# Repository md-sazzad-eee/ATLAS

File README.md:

# ATLAS — Phase 1 foundation

Modular multi-robot research assistant: a carrier (ATLAS-M) that transports two agents
(ATLAS-S1 Scout, ATLAS-S2 Research), deploys them, collects their results, re-plans when
something fails, and tracks which conclusions depend on which evidence.

Phase 1 is the design and simulation stage. Nothing here is a measured hardware result.
Every number comes from `00_requirements/atlas_params.yaml` and is a **proposed target**.

## One source of truth

```
00_requirements/atlas_params.yaml   <- edit this only
python3 00_requirements/sync_params.py   -> atlas_params.json (+ interface checks)
```

MATLAB, FreeCAD and the Python simulator all read `atlas_params.json`. `sync_params.py`
refuses inconsistent interfaces, for example funnels that overlap, wheels that hit the
bays, or a bay shorter than the agent.

## What is here and how to run it

| Area | Tool | Entry point | Output |
|---|---|---|---|
| Drivetrain + energy sizing | MATLAB | `05_simulation/matlab/atlas_sizing.m` | `results/sizing_report.txt`, plots |
| Wheel-speed control loop | Simulink | `05_simulation/matlab/build_speed_loop.m` | `atlas_wheel_speed_loop.slx`, step/load plot |
| Docking state machine | Stateflow | `build_docking_fsm.m`, then `run_docking_tests.m` | `atlas_docking_fsm.slx`, 8 scenario tests, traces |
| Dock contact heating | MATLAB PDE Toolbox | `05_simulation/matlab/contact_heating.m` | `results/contact_heating.*` |
| Parametric CAD | FreeCAD | `01_mechanical/scripts/build_atlas_cad.py` | `.FCStd`, STEP, test-coupon STL, `cad_check.json` |
| Mission intelligence + fleet sim | Python | `05_simulation/python/run_experiments.py` | `results/summary.md`, plot |
| Tests | pytest | `cd 05_simulation/python && python3 -m pytest` | 33 tests |

To run FreeCAD, execute the script from FreeCAD's Python console:
`exec(open('<ATLAS>/01_mechanical/scripts/build_atlas_cad.py').read(), {'__file__': '<that path>'})`

Python needs `numpy scipy networkx pyyaml pydantic matplotlib pytest`.

## Phase 1 findings (what the models changed)

1. **Skid-steer turning sets the carrier motor size.** An in-place turn needs about 3.7×
   the straight-line torque. Widening the track from 300 to 400 mm cut that requirement
   from 0.80 to 0.64 N·m per wheel. Spec per wheel: at least 0.64 N·m continuous and at
   least 95 rpm loaded.
2. **The dock ramp sets the agent motor size.** Climbing the 12° ramp needs 3× the
   flat-floor torque. Spec per wheel: at least 0.10 N·m continuous and at least 73 rpm.
3. **The interface checks caught three geometry errors:**
   - Carrier wheels intruded into the bays, so the wheels moved outboard.
   - The bay was shorter than the agent, so the guides were lengthened to 120 mm.
   - The side latch hit the chassis wall and the neighbouring bay, so it was redesigned
     as a front catch-tab latch. The new latch needed 9.5 mm of pin travel against 8 mm
     available, so the travel spec is now 10 mm.
4. **Contact heating:** about 48 °C at 1 A with a healthy contact. A contaminated contact
   (200 mΩ) reaches about 177 °C at 2 A. Board C should therefore measure the voltage
   drop across the contacts and inhibit charging above about 100 mΩ. Print the contact
   block in PETG, ASA or nylon, not PLA.
5. **Evidence-aware re-planning** (300 paired Monte-Carlo runs). In runs with sensor
   drift:
   - Wrong conclusions: 21% of runs with reassignment alone, 0% with evidence-aware
     re-planning.
   - Recovery cost: about half the re-measurements of a "redo everything" policy, and
     about 3 minutes shorter missions.
   - The carrier never moved with an unlatched agent and no battery-reserve violations
     occurred across all runs.
6. **The batteries are oversized for a 30-minute target:** the agents have about 5 h of
   runtime and the carrier about 6 h. Either downsize (for example a 2S 1000 mAh agent
   pack) or raise the runtime target. Recharging both agents from the carrier uses 40% of
   the carrier's energy.

## Verification done

- The Stateflow chart passes 8 fault scenarios with 3 safety invariants checked on every sample.
- The Python docking FSM reproduces the Stateflow traces sample-for-sample (parity test).
  A deliberate mutation of the Python FSM makes that test fail, so the test does detect differences.
- The FreeCAD interference and clearance report is in `01_mechanical/docking_system/cad_check.json`.
- The blueprint §11 acceptance tests run as simulation tests in `tests/test_blueprint_section11.py`.

## Subsystems

### Dock contact heating (COMSOL)
- `05_simulation/comsol/ContactHeating.java` reproduces the MATLAB result (θ = 156 K/W, 47.8 °C at 1 A, 177 °C at 2 A / 200 mΩ).
- A realistic model that includes the agent side gives 43.6 °C at the design point and 105.7 °C with a contaminated contact.
- `AddPlots.java` adds the temperature and current-density plots to both saved models.

### Camera
ESP32-S3 on every agent. The Scout adds a power-gated Raspberry Pi Zero 2 W + Camera Module 3
(`07_documentation/camera_architecture.md`). Scout runtime with the camera on is about 3.7 h (`atlas_sizing.m`, params v0.1.3).

### Electronics (KiCad, `02_electronics/`)
Every board is specified in Python; the schematic is generated from the spec and the exported netlist is checked against it pin-for-pin.

| Board | Function | Layers | Result |
|---|---|---|---|
| B: agent controller | ESP32-S3, motors, encoders, camera power | 2 | ERC 0/0, DRC 0 errors, 0 unconnected, fab outputs |
| C: dock / charge interface | CC/CV charger per bay, 4-wire contact-resistance monitor | 2 | ERC 0/0, DRC 0 errors, 0 unconnected, fab outputs |
| A: carrier controller | ESP32-S3, 4 wheel drivers, bay interlock in hardware | 4 | ERC 0 errors, DRC 0 errors, 0 unconnected, fab outputs |

Board A puts the "never move with a seated, unlatched agent" rule into logic gates; Board C measures dock contact
resistance by 4-wire sensing. Details and the PCB flow are in `02_electronics/README.md`.

### Firmware (`03_firmware/`)
Agent and carrier application cores in plain C, host-tested against plant models (6022 + 42 + 28 checks, 0 failures).
ESP-IDF ports for Board B and Board A compile with 0 warnings; the Pi Zero vision service has 11 tests.

### ROS 2
A six-package ROS 2 (Jazzy) workspace exists but is not included in this repository yet.

## Further findings

1. The agent's series diode limits a dock charge to about 86 % SOC. An ideal diode on Board B rev B would reach 98 %.
2. Yaw from a single 50 mm AprilTag is unreliable beyond about 0.75 m. Dock alignment should steer on bearing when far out.
3. A 2 s heartbeat timeout lets an agent travel about 0.4 m blind.

## Next phase (bench work)

- Order and assemble Boards A, B and C; flash the ESP32 firmware.
- Motor identification (the agent and carrier PI gains use assumed motors).
- INA226 / ADC calibration and camera calibration.
- Print the clearance coupons; run 100 docking cycles.
- Charge tests with real contacts.

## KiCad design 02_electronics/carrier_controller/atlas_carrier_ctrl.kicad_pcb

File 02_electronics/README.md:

# Electronics

## Board B: ATLAS-S agent controller (shared by S1 and S2), rev A

KiCad 10 project: `agent_controller/atlas_agent_ctrl.kicad_pro`
Design source of truth: `agent_controller/design/board_b_design.py`, which holds every part, value, footprint and pin→net assignment.

| Check | Result |
|---|---|
| Parts / nets | 112 parts, 69 signal nets + 8 intentional no-connects |
| ERC (kicad-cli) | **0 errors, 0 warnings** |
| Schematic vs design spec | `design/verify_netlist.py`: **69/69 nets identical, pin-for-pin** |
| PCB placement | 110 × 90 mm, 2-layer, 4× M3. Courtyard check passes with no overlaps and no off-board parts. ESP32 antenna is flush with the front edge, with a keep-out band |
| Routing | Freerouting 2.1 (local, headless) via `design/run_pcb_pipeline.sh`: 1117 segments, 321 vias, **0 unrouted** |
| DRC (kicad-cli, with schematic parity) | **0 errors, 0 unconnected, 0 parity issues**; 8 cosmetic silkscreen warnings |
| Mechanical fit | Board inside the Scout body (FreeCAD): 5.2 mm above the wheels, 17.4 mm under the lid, 6 mm behind the front wall (`fit_check.json`) |
| Fab outputs | `fab/atlas_agent_ctrl_gerbers.zip` (gerbers + drill), `fab/atlas_agent_ctrl_bom.csv`, `fab/atlas_agent_ctrl_pos.csv`, `atlas_agent_ctrl.step` |

### Architecture

- **Power in:** 2S Li-ion (J1, with NTC), then a 3 A PTC, then a reverse-polarity P-MOSFET (AOD409), then a TVS (SMBJ10CA) and 100 µF bulk.
- **Dock charge path:** J2 pads (VCHG, GND, DATA, ID), then an SS34 diode (no backfeed to the pads), then the charge switch Q2, which the ESP32 can open (`CHG_EN`).
  - The ID resistor R8 sets agent identity: 10 k for S1, 22 k for S2.
  - DATA is a half-duplex UART with 1 k series resistors and ESD protection.
  - Note: the diode drop limits the pack to about 8.0 V (about 90% charge). This is deliberate and conservative.
- **Rails:**
  - **5 V / 3 A:** TPS563201 buck, Vout = 0.768 × (1 + 56k/10k) = 5.07 V. Feeds the Pi module and the sensor connector.
  - **3.3 V / 600 mA:** AP2112K LDO, fed from 5 V or USB VBUS through Schottky OR diodes, so the board can be programmed from USB without a battery.
- **MCU:** ESP32-S3-WROOM-1-N8R8 with native USB-C (ESD-protected), RESET and BOOT buttons, and a UART0 debug header.
  - GPIO35–37 are left unconnected because the N8R8 uses them for octal PSRAM.
  - Strapping pins 45 and 46 are left unconnected.
- **Motors:**
  - Two DRV8871 drivers with ILIM 33 k, giving about 2.0 A current limiting (assumed stall about 1.2 A from the MATLAB sizing).
  - A 20 mΩ high-side shunt feeds an INA180A2 (×50) per motor, so 1 A reads as 1.0 V at the ADC.
  - Encoders have 10 k pull-ups.
- **Independent motor disable:**
  - The motor rail VM_SW is switched by the P-MOSFET Q5.
  - Q5 turns on only when the 74LVC1G08 AND gate sees both `MOT_EN` (firmware) and `WDT_OK` (TPS3823 watchdog, 1.6 s timeout).
  - If the firmware hangs, the motors lose power without any software involved.
- **Scout vision module:** J6 (JST-GH 6P) carries power-gated 5 V and a UART to a Raspberry Pi Zero 2 W + Camera Module 3. See `07_documentation/camera_architecture.md`.
- **Expansion:** Qwiic I2C (J7) for IMU/ToF, and an 8-pin sensor-module connector (J8: 5 V, 3.3 V, I2C, GPIO, ADC) for the Research agent's instrument.
- **Test points:** VBAT, 5 V, 3V3, VM_SW, IMOT_L, IMOT_R, WDT_OK, GND.

### ESP32-S3 pin map

| GPIO | Net | GPIO | Net |
|---|---|---|---|
| 1/2 | I2C SDA/SCL | 15/16 | MOT_L IN1/IN2 |
| 4 | VBAT_SENSE (100k/22k) | 17/18 | LED_STAT / PI_PWR_EN |
| 5/6 | IMOT_L / IMOT_R | 21 | MOT_EN |
| 7 | BATT_NTC | 38 | WDI (watchdog kick) |
| 8 | DOCK_VSENSE | 39/40 | DOCK_TX / DOCK_RX |
| 9/10 | SENS_ADC / SENS_GPIO | 41 | CHG_EN |
| 11/12 | ENC_L A/B | 42 | MOT_R IN2 |
| 13/14 | ENC_R A/B | 47 | MOT_R IN1 |
| 19/20 | USB D−/D+ | 48 / 3 | PI_TX / PI_RX |

*Rev A1: the right-motor inputs moved to right-side module pins (IO47/IO42), swapping with LED_STAT/PI_PWR_EN, because the router could not cross the board from the left-side pins.*

### Rebuilding the board

`design/run_pcb_pipeline.sh` (macOS) runs the whole flow:
1. Place the parts from the spec.
2. Route with Freerouting.
3. Import the routes and add the GND pours and stitching vias.
4. Run up to 3 completion passes for any connection the router missed.
5. Bridge any isolated GND islands.
6. Run DRC.

The spec, the placement and the pipeline are the source. The `.kicad_pcb` is a generated output.
Routing needs a Java 21 runtime; the pipeline uses COMSOL's bundled JRE.

Layout choices:
- **Inset outline for routing.** Freerouting only keeps its 0.2 mm track clearance to the outline, so the DSN is exported with the outline inset 0.4 mm. This gives at least 0.6 mm copper-to-edge on the finished board.
- **GND plane, not routed.** GND is a plane on B.Cu plus a pour on F.Cu, and is not routed as a net.
- **Power class.** Power nets use 0.5 mm tracks. 0.8 mm tracks could not enter SOT-23 pins.

### Known rev-A limitations

- The F.Cu pour uses solid (not thermal-relief) pad connections. This is easier for DRC but harder to hand-solder on large GND pads.
- The schematic is label-driven and block-organised. It is correct (verified), but some value and label text overlaps and could be tidied in Eeschema.
- Motor stall current is assumed, not measured. Measure it before ordering and adjust ILIM (R24/R25).
- Diode-OR losses on the LDO input are about 0.3 V. That's fine at 5 V and should be revisited if the LDO input is ever taken from the battery.

## Shared tool flow (Boards A and C)

All tools are in `02_electronics/tools/`. Each board is defined by one Python spec, and the drawing is generated from it.

1. **`check_design.py`** checks the spec against the KiCad libraries:
   - every symbol exists
   - every spec pin exists on the symbol
   - every symbol pin is assigned
   - every footprint has a pad for every pin
2. **`gen_schematic.py`** writes a label-driven `.kicad_sch` with the same style as Board B. Unused pins get no-connect flags, and PWR_FLAGs are added where needed.
3. **`verify_netlist.py`** compares the `kicad-cli` netlist to the spec, pin-for-pin.
4. **`build_pcb.py`** places the board:
   - edge connectors are fixed
   - the remaining parts are placed greedily next to what they connect to, inside per-channel regions
   - writes a Specctra DSN with a 0.5 mm power class
   - the same commands as Board B handle routing import, GND pours/stitching, island bridging and completion passes
5. **`run_board_flow.sh <board_dir>`** runs the whole sequence: ERC → placement DRC → Freerouting → DRC → gerbers/drill/pos/BOM/STEP.
   - Freerouting is limited to `FR_PASSES` passes and `FR_TIMEOUT` seconds. Freerouting 2.1 never stops on its own while any connection is unroutable.
   - Completion passes route the pads of cut-off GND pour islands as tracks. A completion pass that times out ends the loop (the same input would time out again).
   - `fix_islands` joins GND pins the pours miss: straight/L track, then a grid A* router, then (if the pin is fenced in) A* that crosses a signal track, deletes the crossed piece and locks the new GND copper so the completion pass re-routes the signal.
   - **`route_finish.py`** connects whatever Freerouting leaves open, deterministically: KiCad dumps exact geometry, a numpy grid router (all copper layers, through-vias wherever they fit, net-class widths, clearance, hole spacing, edge and keep-outs) routes each open connection, KiCad applies the result. The flow runs it automatically when `NPY` points at a Python with numpy.
   - `RESUME=1 run_board_flow.sh <board>` restarts at the completion passes on the routed board already on disk.
   - Board config switches: `LAYERS` (2 or 4), `GND_ROUTED` (GND routed as an ordinary net, pours added afterwards), `GND_FANOUT` (pre-routing GND vias, True/False/regex), `GAP` and `PART_GAP` (placement spacing), `TRACK`, `CLEARANCE`, `ZONE_CLEARANCE`.

The flow works with KiCad 7 (Linux) and KiCad 10 (macOS):
- Library differences are aliased: `Q_*MOS` moved from `Device` to `Transistor_FET`, and the USB-C shield pin changed from `S1` to `SH`.
- The TPS3823 symbol is vendored in `tools/atlas_extra.kicad_sym`.

## Board C: dock / charge interface, rev A (`dock_charger/`)

| Check | Result |
|---|---|
| Spec vs libraries | 0 errors |
| Schematic | 131 parts, 63 nets, generated. **Netlist = spec on all nets.** **ERC 0/0 in KiCad 10.** |
| Placement | 90 × 66 mm, 2-layer. Bay 1 on the left half, bay 2 on the right. Placement DRC is clean (copper and edge). |
| Routing | Freerouting routes all signals with 0 DRC errors (KiCad 10). A full DRC on the first complete run gave 0 errors and silkscreen warnings only. |
| **Final** | **ERC 0/0. DRC: 0 errors, 0 unconnected, 0 parity** (warnings are silkscreen only). Fab outputs in `dock_charger/fab/`: gerbers + drill zip, BOM, placement, STEP. |

Fixes made during checking:
- The INA226 footprint is now MSOP-10. KiCad 10 has no `VSSOP-10_3x3mm`; the land pattern is the same.
- 10 Ω input resistors were added on the INA226 inputs. TI recommends them, and they also keep 0.5 mm power tracks off 0.5 mm-pitch pins, which had left 9 connections unroutable.
- Board C uses 0.15 mm clearance. JLCPCB's minimum is 0.127 mm, and the 0.5 mm-pitch MSOP pads have 0.15 mm gaps.
- Mounting holes moved to 4 mm from the edge.
- Symbol/footprint parity: Datasheet and Description fields are now copied, and holes and test points are excluded from the BOM.

### Per-bay circuit

- **CV stage:** TPS54202 buck from the 4S pack. Output is 8.34 V (130k/10.0k, 0.1 %). It is deliberately below 8.40 V, so a shorted agent diode still cannot over-charge the pack.
- **CC loop:** 20 mΩ shunt → INA180A2 → LMV358 integrator against ISET → Schottky + 10k injected into the buck FB node.
  - ISET comes from an MCP4725 DAC through a 2:1 divider, so the hardware ceiling is 1.65 A.
- **Pad switch:** AO3401A. It turns on only when `BAY_EN` (Board A, DOCKED only) AND `KALERT_N` are both true. The INA226 contact-alert trip removes it in hardware.
- **4-wire contact monitor:** each agent pad is touched by a force pin and a separate sense pin. INA226 #2 and #3 read V_force − V_sense = I × R_contact directly, with 2.5 µV resolution. This is the monitor that COMSOL/MATLAB called for.
- **DATA / ID:** half-duplex UART (1k / 10k / ESD) and the ID pull-up for agent identity.

### CC/CV loop simulation (`05_simulation/python/cc_cv_charger_sim.py`, averaged model)

- **Connect into a 40 % pack at ISET = 1 A:** peak 1.12 A, settles in 11 ms.
- **Step 0.5 → 1.0 A:** no overshoot, settles in 0.15 ms. Loop crossover is about 3.4 kHz, well below the buck's own loop.
- **Bad contact (+170 mΩ):** 0.86 A (CV-limited). No runaway.
- **Finding:** the agent's SS34 diode (0.3 V) plus about 0.4 Ω of path resistance ends CC at 62 % SOC. Charging stops at 86 % after 181 min.
  - An ideal-diode controller on Board B rev B would reach 98 % in 175 min. This is recommended.

## Board A: carrier main controller, rev A (`carrier_controller/`)

| Check | Result |
|---|---|
| Spec vs libraries | 0 errors |
| Schematic | 157 parts, 96 nets, generated. **Netlist = spec on 93/93 signal nets.** |
| Placement | 130 × 100 mm. ESP32 body flush with the front edge, with an antenna keep-out on all layers. Wheel channels sit at their connectors. 1.5 mm courtyard gap (2.5 mm around the ESP32) leaves routing channels. Placement DRC is clean. |
| Stack-up | **4 layers** (chosen 2026-10-14): F.Cu signals + GND pour, In1.Cu GND pour, In2.Cu signals, B.Cu signals + GND pour. |
| **Final** | **ERC 0 errors. DRC: 0 errors, 0 unconnected, 0 parity** (11 warnings, all silkscreen-to-edge). Fab outputs in `carrier_controller/fab/`: gerbers (4 copper layers) + drill zip, BOM, placement, STEP. |

Why 4 layers: on 2 layers Freerouting left 3–11 connections open on every run (mostly ESP32 pins) and 1–6 GND pins caged off from the pours by signal tracks, in a different place each run (rounds 9–15). Freerouting 2.1 also fails on a dedicated inner plane (exceptions in its plane search), so all four layers are routed with GND as an ordinary net and the GND pours are filled afterwards. With the wider placement gap the first routing pass finished in 6 minutes with 2 connections open, and one completion pass closed them.

### Main blocks

- **MCU:** ESP32-S3-WROOM-1-**N8**. There is no PSRAM, which frees IO35–37 and lets the board use 33 GPIOs.
- **Power:** XT60 → 15 A fuse → reverse-polarity FET → TVS. TPS54302 makes 5 V / 3 A; AP2112K makes 3.3 V (OR-ed with USB).
- **Wheels:** 4× DRV8871 with ILIM 2.9 A. Each side's two drivers share IN1/IN2, so all four wheels are driven with only 4 PWM pins. Each wheel has an INA180A1 current sense and its own PCNT encoder.
- **Hardware interlock:** the motor rail is on only if `MOT_EN` · `WDT_OK` · `ESTOP_OK` · NAND(SEATED₁, LATCHED_N₁) · NAND(SEATED₂, LATCHED_N₂).
  - The carrier therefore **physically cannot drive while an agent is seated but unlatched**. This is the Stateflow invariant implemented in logic gates.
  - The sensors are wired fail-safe: a cut wire reads as "seated" and "not latched".
- **Latches:** 12 V solenoids on the IO45/IO46 strap pins, which are low at reset, so the latch stays locked by its spring.
- **I/O expander:** TCA9534 reads the bay sensors and Board C alerts, and drives the LED and buzzer.
- **Link to the ROS 2 computer:** USB-C.

Firmware for both boards: `03_firmware/carrier_core` + `carrier_esp32s3`. Board C has no MCU; Board A drives it.

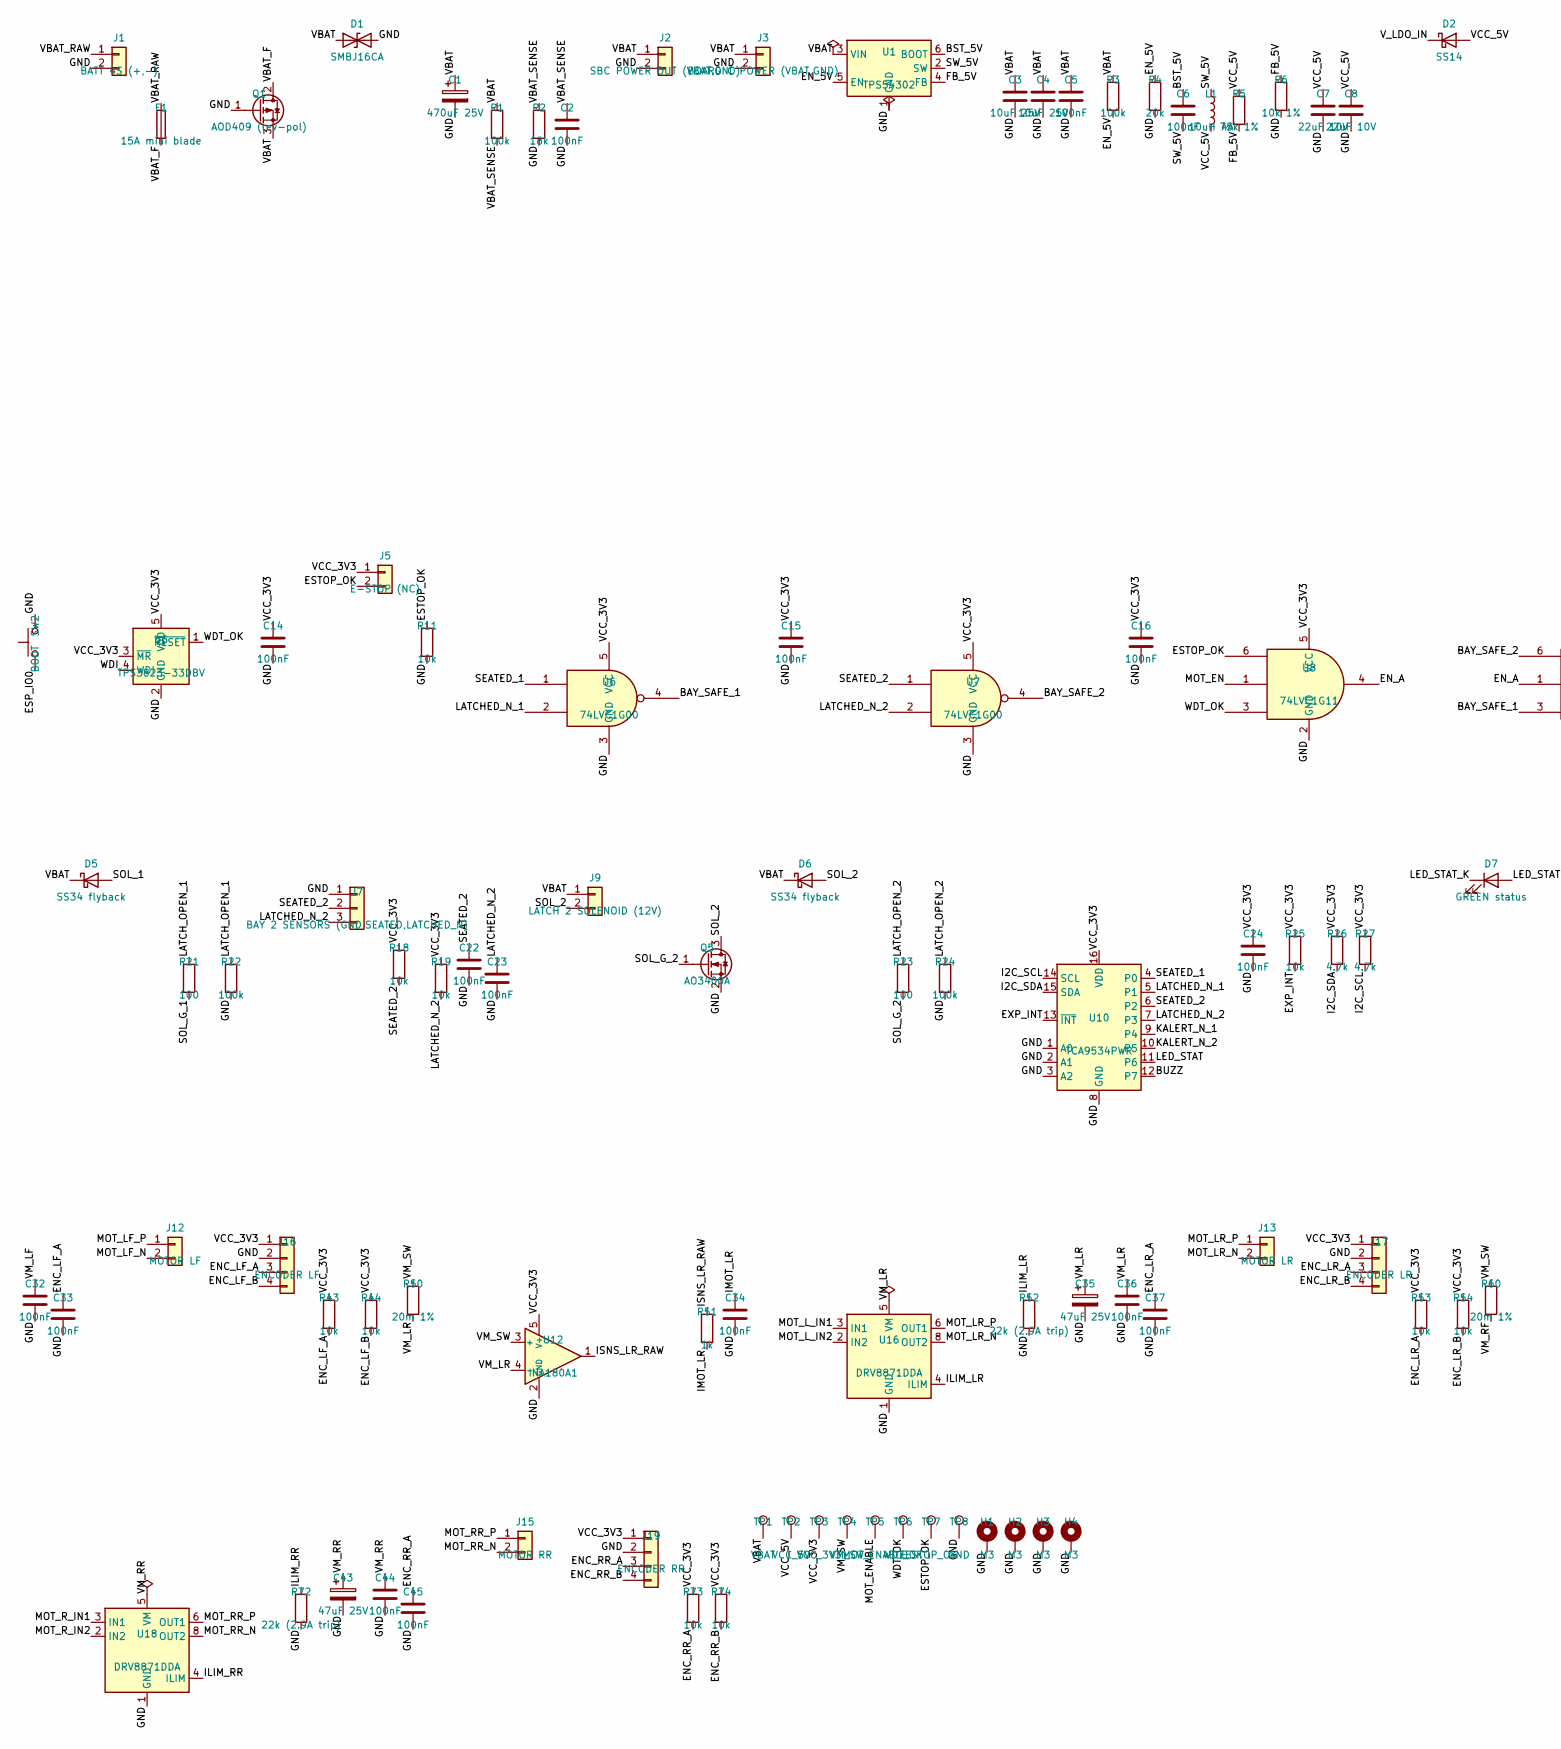
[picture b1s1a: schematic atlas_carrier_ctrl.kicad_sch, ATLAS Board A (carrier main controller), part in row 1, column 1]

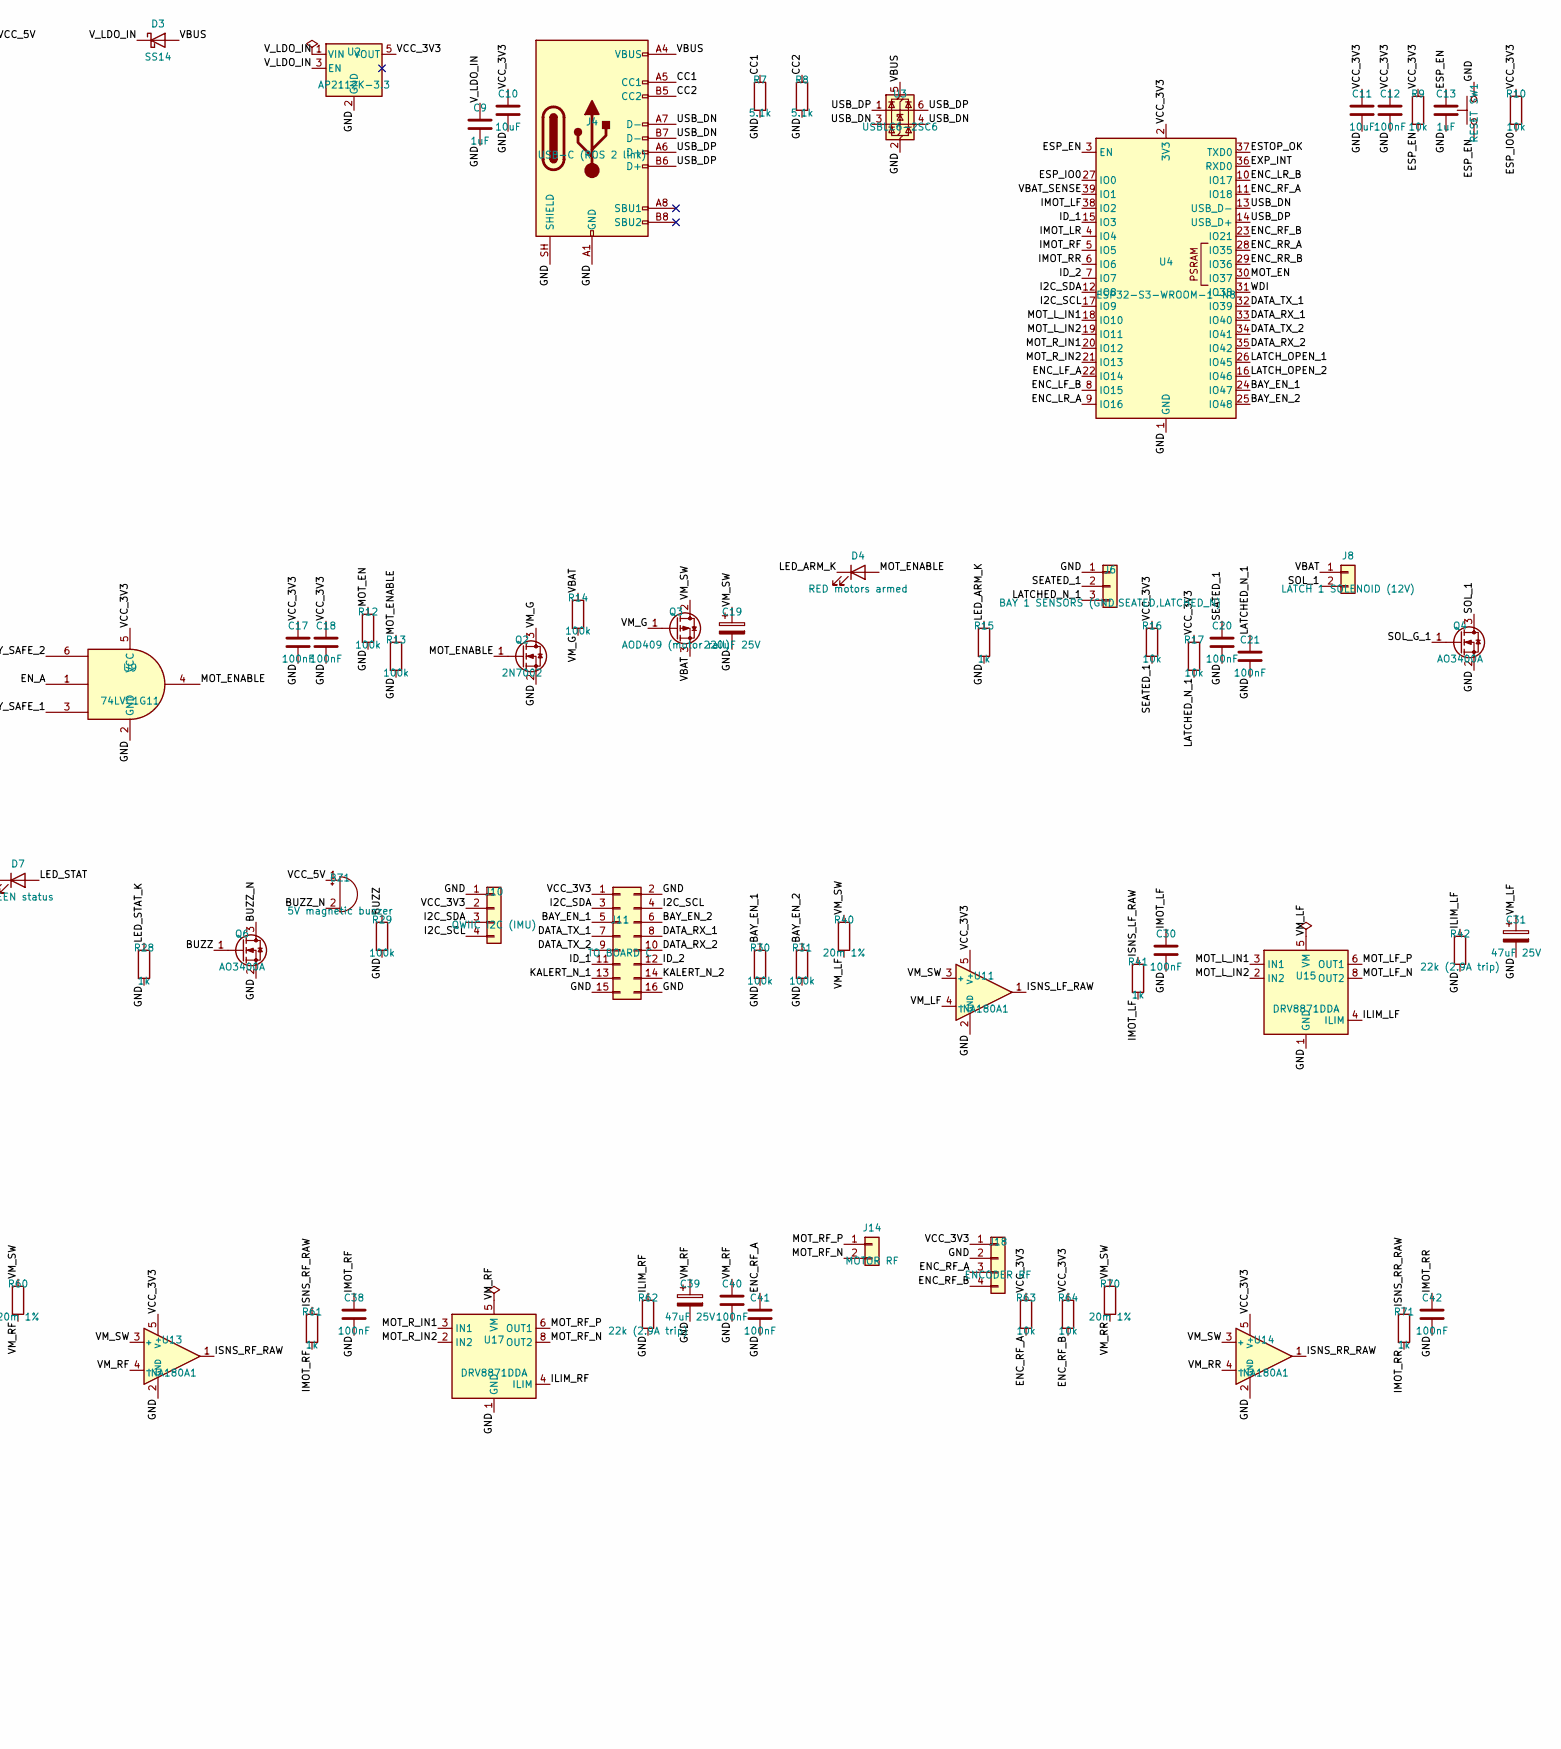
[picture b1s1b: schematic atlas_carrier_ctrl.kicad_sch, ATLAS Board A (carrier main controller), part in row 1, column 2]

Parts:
BZ1: 5V magnetic buzzer; Buzzer_12x9.5RM7.6
C1: 470uF 25V; CP_Elec_10x10.5
C2, C5, C6, C12, C14, C15, C16, C17, C18, C20, C21, C22, C23, C24, C30, C32, C33, C34, C36, C37, C38, C40, C41, C42, C44, C45: 100nF; C_0603_1608Metric
C3, C4: 10uF 25V; C_1206_3216Metric
C7, C8: 22uF 10V; C_1206_3216Metric
C9, C13: 1uF; C_0603_1608Metric
C10, C11: 10uF; C_0805_2012Metric
C19: 220uF 25V; CP_Elec_8x10
C31, C35, C39, C43: 47uF 25V; CP_Elec_6.3x7.7
D1: SMBJ16CA; D_SMB
D2, D3: SS14; D_SMA
D4: RED motors armed; LED_0603_1608Metric
D5, D6: SS34 flyback; D_SMA
D7: GREEN status; LED_0603_1608Metric
F1: 15A mini blade; Fuseholder_Blade_Mini_Keystone_3568
H1, H2, H3, H4: M3; MountingHole_3.2mm_M3_Pad_Via
J1: BATT 4S (+,-); AMASS_XT60PW-M_1x02_P7.20mm_Horizontal
J2: SBC POWER OUT (VBAT,GND); AMASS_XT30PW-M_1x02_P2.50mm_Horizontal
J3: BOARD C POWER (VBAT,GND); AMASS_XT30PW-M_1x02_P2.50mm_Horizontal
J4: USB-C (ROS 2 link); USB_C_Receptacle_GCT_USB4105-xx-A_16P_TopMnt_Horizontal
J5: E-STOP (NC); JST_XH_B2B-XH-A_1x02_P2.50mm_Vertical
J6: BAY 1 SENSORS (GND,SEATED,LATCHED_N); JST_PH_B3B-PH-K_1x03_P2.00mm_Vertical
J7: BAY 2 SENSORS (GND,SEATED,LATCHED_N); JST_PH_B3B-PH-K_1x03_P2.00mm_Vertical
J8: LATCH 1 SOLENOID (12V); JST_VH_B2P-VH_1x02_P3.96mm_Vertical
J9: LATCH 2 SOLENOID (12V); JST_VH_B2P-VH_1x02_P3.96mm_Vertical
J10: QWIIC I2C (IMU); JST_SH_SM04B-SRSS-TB_1x04-1MP_P1.00mm_Horizontal
J11: TO BOARD C; PinHeader_2x08_P2.54mm_Vertical
J12: MOTOR LF; JST_VH_B2P-VH_1x02_P3.96mm_Vertical
J13: MOTOR LR; JST_VH_B2P-VH_1x02_P3.96mm_Vertical
J14: MOTOR RF; JST_VH_B2P-VH_1x02_P3.96mm_Vertical
J15: MOTOR RR; JST_VH_B2P-VH_1x02_P3.96mm_Vertical
J16: ENCODER LF; JST_PH_B4B-PH-K_1x04_P2.00mm_Vertical
J17: ENCODER LR; JST_PH_B4B-PH-K_1x04_P2.00mm_Vertical
J18: ENCODER RF; JST_PH_B4B-PH-K_1x04_P2.00mm_Vertical
J19: ENCODER RR; JST_PH_B4B-PH-K_1x04_P2.00mm_Vertical
L1: 10uH 4A; L_Bourns_SRR1260
Q1: AOD409 (rev-pol); TO-252-2
Q2: 2N7002; SOT-23
Q3: AOD409 (motor rail); TO-252-2
Q4, Q5, Q6: AO3400A; SOT-23
R1, R3, R12, R13, R14, R22, R24, R29, R30, R31: 100k; R_0603_1608Metric
R2: 18k; R_0603_1608Metric
R4: 20k; R_0603_1608Metric
R5: 75k 1%; R_0603_1608Metric
R6: 10k 1%; R_0603_1608Metric
R7, R8: 5.1k; R_0603_1608Metric
R9, R10, R11, R16, R17, R18, R19, R25, R43, R44, R53, R54, R63, R64, R73, R74: 10k; R_0603_1608Metric
R15, R28, R41, R51, R61, R71: 1k; R_0603_1608Metric
R21, R23: 100; R_0603_1608Metric
R26, R27: 4.7k; R_0603_1608Metric
R40, R50, R60, R70: 20m 1%; R_1206_3216Metric
R42, R52, R62, R72: 22k (2.9A trip); R_0603_1608Metric
SW1: RESET; SW_SPST_TL3342
SW2: BOOT; SW_SPST_TL3342
TP1: VBAT; TestPoint_Pad_D1.5mm
TP2: VCC_5V; TestPoint_Pad_D1.5mm
TP3: VCC_3V3; TestPoint_Pad_D1.5mm
TP4: VM_SW; TestPoint_Pad_D1.5mm
TP5: MOT_ENABLE; TestPoint_Pad_D1.5mm
TP6: WDT_OK; TestPoint_Pad_D1.5mm
TP7: ESTOP_OK; TestPoint_Pad_D1.5mm
TP8: GND; TestPoint_Pad_D1.5mm
U1: TPS54302; SOT-23-6
U2: AP2112K-3.3; SOT-23-5
U3: USBLC6-2SC6; SOT-23-6
U4: ESP32-S3-WROOM-1-N8; ESP32-S3-WROOM-1
U5: TPS3823-33DBV; SOT-23-5
U6, U7: 74LVC1G00; SOT-23-5
U8, U9: 74LVC1G11; SOT-23-6
U10: TCA9534PWR; TSSOP-16_4.4x5mm_P0.65mm
U11, U12, U13, U14: INA180A1; SOT-23-5
U15, U16, U17, U18: DRV8871DDA; Texas_HTSOP-8-1EP_3.9x4.9mm_P1.27mm_EP2.95x4.9mm_Mask2.4x3.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

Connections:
/BAY_EN_1: J11.5, R30.1, U4.24 (IO47)
/BAY_EN_2: J11.6, R31.1, U4.25 (IO48)
/BAY_SAFE_1: U6.4, U9.3
/BAY_SAFE_2: U7.4, U9.6
/BST_5V: C6.1, U1.6 (BOOT)
/BUZZ: Q6.1 (G), R29.1, U10.12 (P7)
/BUZZ_N: BZ1.2 (-), Q6.3 (D)
/CC1: J4.A5 (CC1), R7.1
/CC2: J4.B5 (CC2), R8.1
/DATA_RX_1: J11.8, U4.33 (IO40)
/DATA_RX_2: J11.10, U4.35 (IO42)
/DATA_TX_1: J11.7, U4.32 (IO39)
/DATA_TX_2: J11.9, U4.34 (IO41)
/ENC_LF_A: C33.1, J16.3, R43.2, U4.22 (IO14)
/ENC_LF_B: J16.4, R44.2, U4.8 (IO15)
/ENC_LR_A: C37.1, J17.3, R53.2, U4.9 (IO16)
/ENC_LR_B: J17.4, R54.2, U4.10 (IO17)
/ENC_RF_A: C41.1, J18.3, R63.2, U4.11 (IO18)
/ENC_RF_B: J18.4, R64.2, U4.23 (IO21)
/ENC_RR_A: C45.1, J19.3, R73.2, U4.28 (IO35)
/ENC_RR_B: J19.4, R74.2, U4.29 (IO36)
/EN_5V: R3.2, R4.1, U1.5 (EN)
/EN_A: U8.4, U9.1
/ESP_EN: C13.1, R9.2, SW1.1, U4.3 (EN)
/ESP_IO0: R10.2, SW2.1, U4.27 (IO0)
/ESTOP_OK: J5.2, R11.1, TP7.1, U4.37 (TXD0), U8.6
/EXP_INT: R25.2, U4.36 (RXD0), U10.13 (~INT)
/FB_5V: R5.2, R6.1, U1.4 (FB)
/GND: C1.2, C2.2, C3.2, C4.2, C5.2, C7.2, C8.2, C9.2, C10.2, C11.2, C12.2, C13.2, C14.2, C15.2, C16.2, C17.2, C18.2, C19.2, C20.2, C21.2, C22.2, C23.2, C24.2, C30.2, C31.2, C32.2, C33.2, C34.2, C35.2, C36.2, C37.2, C38.2, C39.2, C40.2, C41.2, C42.2, C43.2, C44.2, C45.2, D1.2 (A2), H1.1, H2.1, H3.1, H4.1, J1.2, J2.2, J3.2, J4.A1 (GND), J4.A12 (GND), J4.B1 (GND), J4.B12 (GND), J4.SH (SHIELD), J6.1, J7.1, J10.1, J11.2, J11.15, J11.16, J16.2, J17.2, J18.2, J19.2, Q1.1 (G), Q2.2 (S), Q4.2 (S), Q5.2 (S), Q6.2 (S), R2.2, R4.2, R6.2, R7.2, R8.2, R11.2, R12.2, R13.2, R15.2, R22.2, R24.2, R28.2, R29.2, R30.2, R31.2, R42.2, R52.2, R62.2, R72.2, SW1.2, SW2.2, TP8.1, U1.1 (GND), U2.2 (GND), U3.2 (GND), U4.1 (GND), U4.40 (GND), U4.41 (GND), U5.2 (GND), U6.3 (GND), U7.3 (GND), U8.2 (GND), U9.2 (GND), U10.1 (A0), U10.2 (A1), U10.3 (A2), U10.8 (GND), U11.2 (GND), U12.2 (GND), U13.2 (GND), U14.2 (GND), U15.1 (GND), U15.7 (GND), U15.9 (GND), U16.1 (GND), U16.7 (GND), U16.9 (GND), U17.1 (GND), U17.7 (GND), U17.9 (GND), U18.1 (GND), U18.7 (GND), U18.9 (GND)
/I2C_SCL: J10.4, J11.4, R27.2, U4.17 (IO9), U10.14 (SCL)
/I2C_SDA: J10.3, J11.3, R26.2, U4.12 (IO8), U10.15 (SDA)
/ID_1: J11.11, U4.15 (IO3)
/ID_2: J11.12, U4.7 (IO7)
/ILIM_LF: R42.1, U15.4 (ILIM)
/ILIM_LR: R52.1, U16.4 (ILIM)
/ILIM_RF: R62.1, U17.4 (ILIM)
/ILIM_RR: R72.1, U18.4 (ILIM)
/IMOT_LF: C30.1, R41.2, U4.38 (IO2)
/IMOT_LR: C34.1, R51.2, U4.4 (IO4)
/IMOT_RF: C38.1, R61.2, U4.5 (IO5)
/IMOT_RR: C42.1, R71.2, U4.6 (IO6)
/ISNS_LF_RAW: R41.1, U11.1
/ISNS_LR_RAW: R51.1, U12.1
/ISNS_RF_RAW: R61.1, U13.1
/ISNS_RR_RAW: R71.1, U14.1
/KALERT_N_1: J11.13, U10.9 (P4)
/KALERT_N_2: J11.14, U10.10 (P5)
/LATCHED_N_1: C21.1, J6.3, R17.2, U6.2, U10.5 (P1)
/LATCHED_N_2: C23.1, J7.3, R19.2, U7.2, U10.7 (P3)
/LATCH_OPEN_1: R21.1, R22.1, U4.26 (IO45)
/LATCH_OPEN_2: R23.1, R24.1, U4.16 (IO46)
/LED_ARM_K: D4.1 (K), R15.1
/LED_STAT: D7.2 (A), U10.11 (P6)
/LED_STAT_K: D7.1 (K), R28.1
/MOT_EN: R12.1, U4.30 (IO37), U8.1
/MOT_ENABLE: D4.2 (A), Q2.1 (G), R13.1, TP5.1, U9.4
/MOT_LF_N: J12.2, U15.8 (OUT2)
/MOT_LF_P: J12.1, U15.6 (OUT1)
/MOT_LR_N: J13.2, U16.8 (OUT2)
/MOT_LR_P: J13.1, U16.6 (OUT1)
/MOT_L_IN1: U4.18 (IO10), U15.3 (IN1), U16.3 (IN1)
/MOT_L_IN2: U4.19 (IO11), U15.2 (IN2), U16.2 (IN2)
/MOT_RF_N: J14.2, U17.8 (OUT2)
/MOT_RF_P: J14.1, U17.6 (OUT1)
/MOT_RR_N: J15.2, U18.8 (OUT2)
/MOT_RR_P: J15.1, U18.6 (OUT1)
/MOT_R_IN1: U4.20 (IO12), U17.3 (IN1), U18.3 (IN1)
/MOT_R_IN2: U4.21 (IO13), U17.2 (IN2), U18.2 (IN2)
/SEATED_1: C20.1, J6.2, R16.2, U6.1, U10.4 (P0)
/SEATED_2: C22.1, J7.2, R18.2, U7.1, U10.6 (P2)
/SOL_1: D5.2 (A), J8.2, Q4.3 (D)
/SOL_2: D6.2 (A), J9.2, Q5.3 (D)
/SOL_G_1: Q4.1 (G), R21.2
/SOL_G_2: Q5.1 (G), R23.2
/SW_5V: C6.2, L1.1, U1.2 (SW)
/USB_DN: J4.A7 (D-), J4.B7 (D-), U3.3 (I/O2), U3.4 (I/O2), U4.13 (USB_D-)
/USB_DP: J4.A6 (D+), J4.B6 (D+), U3.1 (I/O1), U3.6 (I/O1), U4.14 (USB_D+)
/VBAT: C1.1, C3.1, C4.1, C5.1, D1.1 (A1), D5.1 (K), D6.1 (K), J2.1, J3.1, J8.1, J9.1, Q1.3 (S), Q3.3 (S), R1.1, R3.1, R14.1, TP1.1, U1.3 (VIN)
/VBAT_F: F1.2, Q1.2 (D)
/VBAT_RAW: F1.1, J1.1
/VBAT_SENSE: C2.1, R1.2, R2.1, U4.39 (IO1)
/VBUS: D3.2 (A), J4.A4 (VBUS), J4.A9 (VBUS), J4.B4 (VBUS), J4.B9 (VBUS), U3.5 (VBUS)
/VCC_3V3: C10.1, C11.1, C12.1, C14.1, C15.1, C16.1, C17.1, C18.1, C24.1, J5.1, J10.2, J11.1, J16.1, J17.1, J18.1, J19.1, R9.1, R10.1, R16.1, R17.1, R18.1, R19.1, R25.1, R26.1, R27.1, R43.1, R44.1, R53.1, R54.1, R63.1, R64.1, R73.1, R74.1, TP3.1, U2.5 (VOUT), U4.2 (3V3), U5.3 (~MR), U5.5 (VDD), U6.5 (VCC), U7.5 (VCC), U8.5 (VCC), U9.5 (VCC), U10.16 (VDD), U11.5 (V+), U12.5 (V+), U13.5 (V+), U14.5 (V+)
/VCC_5V: BZ1.1 (+), C7.1, C8.1, D2.2 (A), L1.2, R5.1, TP2.1
/VM_G: Q2.3 (D), Q3.1 (G), R14.2
/VM_LF: C31.1, C32.1, R40.2, U11.4 (-), U15.5 (VM)
/VM_LR: C35.1, C36.1, R50.2, U12.4 (-), U16.5 (VM)
/VM_RF: C39.1, C40.1, R60.2, U13.4 (-), U17.5 (VM)
/VM_RR: C43.1, C44.1, R70.2, U14.4 (-), U18.5 (VM)
/VM_SW: C19.1, Q3.2 (D), R40.1, R50.1, R60.1, R70.1, TP4.1, U11.3 (+), U12.3 (+), U13.3 (+), U14.3 (+)
/V_LDO_IN: C9.1, D2.1 (K), D3.1 (K), U2.1 (VIN), U2.3 (EN)
/WDI: U4.31 (IO38), U5.4 (WDI)
/WDT_OK: TP6.1, U5.1 (~RESET), U8.3

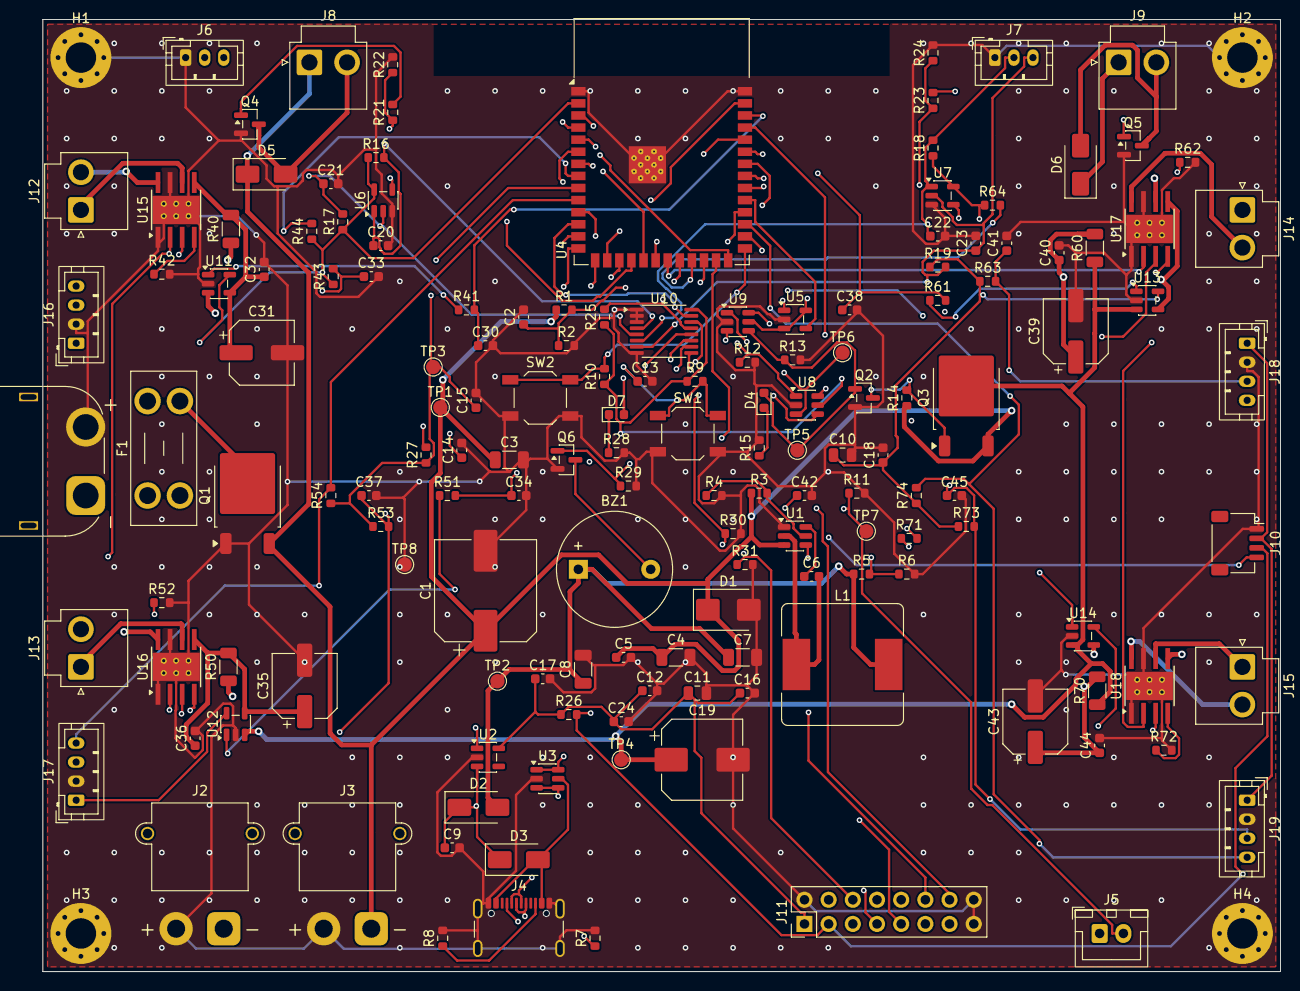
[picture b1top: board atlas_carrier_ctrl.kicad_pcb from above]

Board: 4 copper layers, 130.0 x 100.0 mm, 157 parts (0 on the bottom side), 93 nets.

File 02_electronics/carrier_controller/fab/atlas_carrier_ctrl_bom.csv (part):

"Refs","Value","Footprint","Qty","DNP"
"BZ1","5V magnetic buzzer","Buzzer_Beeper:Buzzer_12x9.5RM7.6","1",""
"C1","470uF 25V","Capacitor_SMD:CP_Elec_10x10.5","1",""
"C2","100nF","Capacitor_SMD:C_0603_1608Metric","1",""
"C3","10uF 25V","Capacitor_SMD:C_1206_3216Metric","1",""
"C4","10uF 25V","Capacitor_SMD:C_1206_3216Metric","1",""
"C5","100nF","Capacitor_SMD:C_0603_1608Metric","1",""
"C6","100nF","Capacitor_SMD:C_0603_1608Metric","1",""
"C7","22uF 10V","Capacitor_SMD:C_1206_3216Metric","1",""
"C8","22uF 10V","Capacitor_SMD:C_1206_3216Metric","1",""
"C9","1uF","Capacitor_SMD:C_0603_1608Metric","1",""
"C10","10uF","Capacitor_SMD:C_0805_2012Metric","1",""
"C11","10uF","Capacitor_SMD:C_0805_2012Metric","1",""
"C12","100nF","Capacitor_SMD:C_0603_1608Metric","1",""
"C13","1uF","Capacitor_SMD:C_0603_1608Metric","1",""
"C14","100nF","Capacitor_SMD:C_0603_1608Metric","1",""
"C15","100nF","Capacitor_SMD:C_0603_1608Metric","1",""
"C16","100nF","Capacitor_SMD:C_0603_1608Metric","1",""
"C17","100nF","Capacitor_SMD:C_0603_1608Metric","1",""
"C18","100nF","Capacitor_SMD:C_0603_1608Metric","1",""
"C19","220uF 25V","Capacitor_SMD:CP_Elec_8x10","1",""
"C20","100nF","Capacitor_SMD:C_0603_1608Metric","1",""
"C21","100nF","Capacitor_SMD:C_0603_1608Metric","1",""
"C22","100nF","Capacitor_SMD:C_0603_1608Metric","1",""
"C23","100nF","Capacitor_SMD:C_0603_1608Metric","1",""
"C24","100nF","Capacitor_SMD:C_0603_1608Metric","1",""
"C30","100nF","Capacitor_SMD:C_0603_1608Metric","1",""
"C31","47uF 25V","Capacitor_SMD:CP_Elec_6.3x7.7","1",""
"C32","100nF","Capacitor_SMD:C_0603_1608Metric","1",""
"C33","100nF","Capacitor_SMD:C_0603_1608Metric","1",""
"C34","100nF","Capacitor_SMD:C_0603_1608Metric","1",""
"C35","47uF 25V","Capacitor_SMD:CP_Elec_6.3x7.7","1",""
"C36","100nF","Capacitor_SMD:C_0603_1608Metric","1",""
"C37","100nF","Capacitor_SMD:C_0603_1608Metric","1",""
"C38","100nF","Capacitor_SMD:C_0603_1608Metric","1",""
"C39","47uF 25V","Capacitor_SMD:CP_Elec_6.3x7.7","1",""
"C40","100nF","Capacitor_SMD:C_0603_1608Metric","1",""
"C41","100nF","Capacitor_SMD:C_0603_1608Metric","1",""
"C42","100nF","Capacitor_SMD:C_0603_1608Metric","1",""
"C43","47uF 25V","Capacitor_SMD:CP_Elec_6.3x7.7","1",""
"C44","100nF","Capacitor_SMD:C_0603_1608Metric","1",""
"C45","100nF","Capacitor_SMD:C_0603_1608Metric","1",""
"D1","SMBJ16CA","Diode_SMD:D_SMB","1",""
"D2","SS14","Diode_SMD:D_SMA","1",""
"D3","SS14","Diode_SMD:D_SMA","1",""
"D4","RED motors armed","LED_SMD:LED_0603_1608Metric","1",""
"D5","SS34 flyback","Diode_SMD:D_SMA","1",""
"D6","SS34 flyback","Diode_SMD:D_SMA","1",""
"D7","GREEN status","LED_SMD:LED_0603_1608Metric","1",""
"F1","15A mini blade","Fuse:Fuseholder_Blade_Mini_Keystone_3568","1",""
"J1","BATT 4S (+,-)","Connector_AMASS:AMASS_XT60PW-M_1x02_P7.20mm_Horizontal","1",""
"J2","SBC POWER OUT (VBAT,GND)","Connector_AMASS:AMASS_XT30PW-M_1x02_P2.50mm_Horizontal","1",""
"J3","BOARD C POWER (VBAT,GND)","Connector_AMASS:AMASS_XT30PW-M_1x02_P2.50mm_Horizontal","1",""
"J4","USB-C (ROS 2 link)","Connector_USB:USB_C_Receptacle_GCT_USB4105-xx-A_16P_TopMnt_Horizontal","1",""
"J5","E-STOP (NC)","Connector_JST:JST_XH_B2B-XH-A_1x02_P2.50mm_Vertical","1",""
"J6","BAY 1 SENSORS (GND,SEATED,LATCHED_N)","Connector_JST:JST_PH_B3B-PH-K_1x03_P2.00mm_Vertical","1",""
"J7","BAY 2 SENSORS (GND,SEATED,LATCHED_N)","Connector_JST:JST_PH_B3B-PH-K_1x03_P2.00mm_Vertical","1",""
"J8","LATCH 1 SOLENOID (12V)","Connector_JST:JST_VH_B2P-VH_1x02_P3.96mm_Vertical","1",""
"J9","LATCH 2 SOLENOID (12V)","Connector_JST:JST_VH_B2P-VH_1x02_P3.96mm_Vertical","1",""
"J10","QWIIC I2C (IMU)","Connector_JST:JST_SH_SM04B-SRSS-TB_1x04-1MP_P1.00mm_Horizontal","1",""
"J11","TO BOARD C","Connector_PinHeader_2.54mm:PinHeader_2x08_P2.54mm_Vertical","1",""
"J12","MOTOR LF","Connector_JST:JST_VH_B2P-VH_1x02_P3.96mm_Vertical","1",""
"J13","MOTOR LR","Connector_JST:JST_VH_B2P-VH_1x02_P3.96mm_Vertical","1",""
"J14","MOTOR RF","Connector_JST:JST_VH_B2P-VH_1x02_P3.96mm_Vertical","1",""
"J15","MOTOR RR","Connector_JST:JST_VH_B2P-VH_1x02_P3.96mm_Vertical","1",""
"J16","ENCODER LF","Connector_JST:JST_PH_B4B-PH-K_1x04_P2.00mm_Vertical","1",""
"J17","ENCODER LR","Connector_JST:JST_PH_B4B-PH-K_1x04_P2.00mm_Vertical","1",""
"J18","ENCODER RF","Connector_JST:JST_PH_B4B-PH-K_1x04_P2.00mm_Vertical","1",""
"J19","ENCODER RR","Connector_JST:JST_PH_B4B-PH-K_1x04_P2.00mm_Vertical","1",""
"L1","10uH 4A","Inductor_SMD:L_Bourns_SRR1260","1",""
"Q1","AOD409 (rev-pol)","Package_TO_SOT_SMD:TO-252-2","1",""
"Q2","2N7002","Package_TO_SOT_SMD:SOT-23","1",""
"Q3","AOD409 (motor rail)","Package_TO_SOT_SMD:TO-252-2","1",""
"Q4","AO3400A","Package_TO_SOT_SMD:SOT-23","1",""
"Q5","AO3400A","Package_TO_SOT_SMD:SOT-23","1",""
"Q6","AO3400A","Package_TO_SOT_SMD:SOT-23","1",""
"R1","100k","Resistor_SMD:R_0603_1608Metric","1",""
"R2","18k","Resistor_SMD:R_0603_1608Metric","1",""
"R3","100k","Resistor_SMD:R_0603_1608Metric","1",""
"R4","20k","Resistor_SMD:R_0603_1608Metric","1",""
"R5","75k 1%","Resistor_SMD:R_0603_1608Metric","1",""
"R6","10k 1%","Resistor_SMD:R_0603_1608Metric","1",""
"R7","5.1k","Resistor_SMD:R_0603_1608Metric","1",""
"R8","5.1k","Resistor_SMD:R_0603_1608Metric","1",""
"R9","10k","Resistor_SMD:R_0603_1608Metric","1",""
"R10","10k","Resistor_SMD:R_0603_1608Metric","1",""
"R11","10k","Resistor_SMD:R_0603_1608Metric","1",""
"R12","100k","Resistor_SMD:R_0603_1608Metric","1",""
"R13","100k","Resistor_SMD:R_0603_1608Metric","1",""
"R14","100k","Resistor_SMD:R_0603_1608Metric","1",""
"R15","1k","Resistor_SMD:R_0603_1608Metric","1",""
"R16","10k","Resistor_SMD:R_0603_1608Metric","1",""
"R17","10k","Resistor_SMD:R_0603_1608Metric","1",""
"R18","10k","Resistor_SMD:R_0603_1608Metric","1",""
"R19","10k","Resistor_SMD:R_0603_1608Metric","1",""
"R21","100","Resistor_SMD:R_0603_1608Metric","1",""
"R22","100k","Resistor_SMD:R_0603_1608Metric","1",""
"R23","100","Resistor_SMD:R_0603_1608Metric","1",""
"R24","100k","Resistor_SMD:R_0603_1608Metric","1",""
"R25","10k","Resistor_SMD:R_0603_1608Metric","1",""
"R26","4.7k","Resistor_SMD:R_0603_1608Metric","1",""
"R27","4.7k","Resistor_SMD:R_0603_1608Metric","1",""
"R28","1k","Resistor_SMD:R_0603_1608Metric","1",""
"R29","100k","Resistor_SMD:R_0603_1608Metric","1",""
"R30","100k","Resistor_SMD:R_0603_1608Metric","1",""
"R31","100k","Resistor_SMD:R_0603_1608Metric","1",""
"R40","20m 1%","Resistor_SMD:R_1206_3216Metric","1",""
"R41","1k","Resistor_SMD:R_0603_1608Metric","1",""
"R42","22k (2.9A trip)","Resistor_SMD:R_0603_1608Metric","1",""
"R43","10k","Resistor_SMD:R_0603_1608Metric","1",""
"R44","10k","Resistor_SMD:R_0603_1608Metric","1",""
"R50","20m 1%","Resistor_SMD:R_1206_3216Metric","1",""
"R51","1k","Resistor_SMD:R_0603_1608Metric","1",""
"R52","22k (2.9A trip)","Resistor_SMD:R_0603_1608Metric","1",""
"R53","10k","Resistor_SMD:R_0603_1608Metric","1",""
"R54","10k","Resistor_SMD:R_0603_1608Metric","1",""
"R60","20m 1%","Resistor_SMD:R_1206_3216Metric","1",""
"R61","1k","Resistor_SMD:R_0603_1608Metric","1",""
"R62","22k (2.9A trip)","Resistor_SMD:R_0603_1608Metric","1",""
"R63","10k","Resistor_SMD:R_0603_1608Metric","1",""
"R64","10k","Resistor_SMD:R_0603_1608Metric","1",""
"R70","20m 1%","Resistor_SMD:R_1206_3216Metric","1",""
"R71","1k","Resistor_SMD:R_0603_1608Metric","1",""
"R72","22k (2.9A trip)","Resistor_SMD:R_0603_1608Metric","1",""
"R73","10k","Resistor_SMD:R_0603_1608Metric","1",""
"R74","10k","Resistor_SMD:R_0603_1608Metric","1",""
"SW1","RESET","Button_Switch_SMD:SW_SPST_TL3342","1",""
"SW2","BOOT","Button_Switch_SMD:SW_SPST_TL3342","1",""
"U1","TPS54302","Package_TO_SOT_SMD:SOT-23-6","1",""
"U2","AP2112K-3.3","Package_TO_SOT_SMD:SOT-23-5","1",""
"U3","USBLC6-2SC6","Package_TO_SOT_SMD:SOT-23-6","1",""
"U4","ESP32-S3-WROOM-1-N8","RF_Module:ESP32-S3-WROOM-1","1",""
"U5","TPS3823-33DBV","Package_TO_SOT_SMD:SOT-23-5","1",""
"U6","74LVC1G00","Package_TO_SOT_SMD:SOT-23-5","1",""
"U7","74LVC1G00","Package_TO_SOT_SMD:SOT-23-5","1",""
"U8","74LVC1G11","Package_TO_SOT_SMD:SOT-23-6","1",""
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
